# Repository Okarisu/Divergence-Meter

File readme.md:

# Divergence meter

## from Steins;Gate series and visual novels

## Note - this `readme` is in process of writing, the same as the code

## Basic synopsis

In this project I am trying to build working prototype of Divergence meter that appeared in Steins;Gate anime series and Visual novels.

I use arduino board in combination with shift registers SN74HC595N to drive itrons IV-6.

## byte values for shift registers

### Grids

| Itron No. | byte value |
| --------- | ---------- |
| first |  B01111111 |
| second | B10111111 |
| third | B11011111 |
| fourth | B11101111 |
| fifth | B11110111 |
| sixth | B11111011 |
| seventh | B11111101 |
| eighth | B11111110 |

### Numbers & symbols

| Number | byte value |
| ------ | ---------- |
| zero | B00000011 |
| one | B10011111 |
| two | B00100101 |
| three | B00001101 |
| four | B10110001 |
| five | B01001001 |
| six | B01000001 |
| seven | B00011111 |
| eight | B00000001 |
| nine | B00001001 |

| symbol | byte value |
| ------ | ---------- |
| dot | B11111110 |
| stroke | B11111101 |

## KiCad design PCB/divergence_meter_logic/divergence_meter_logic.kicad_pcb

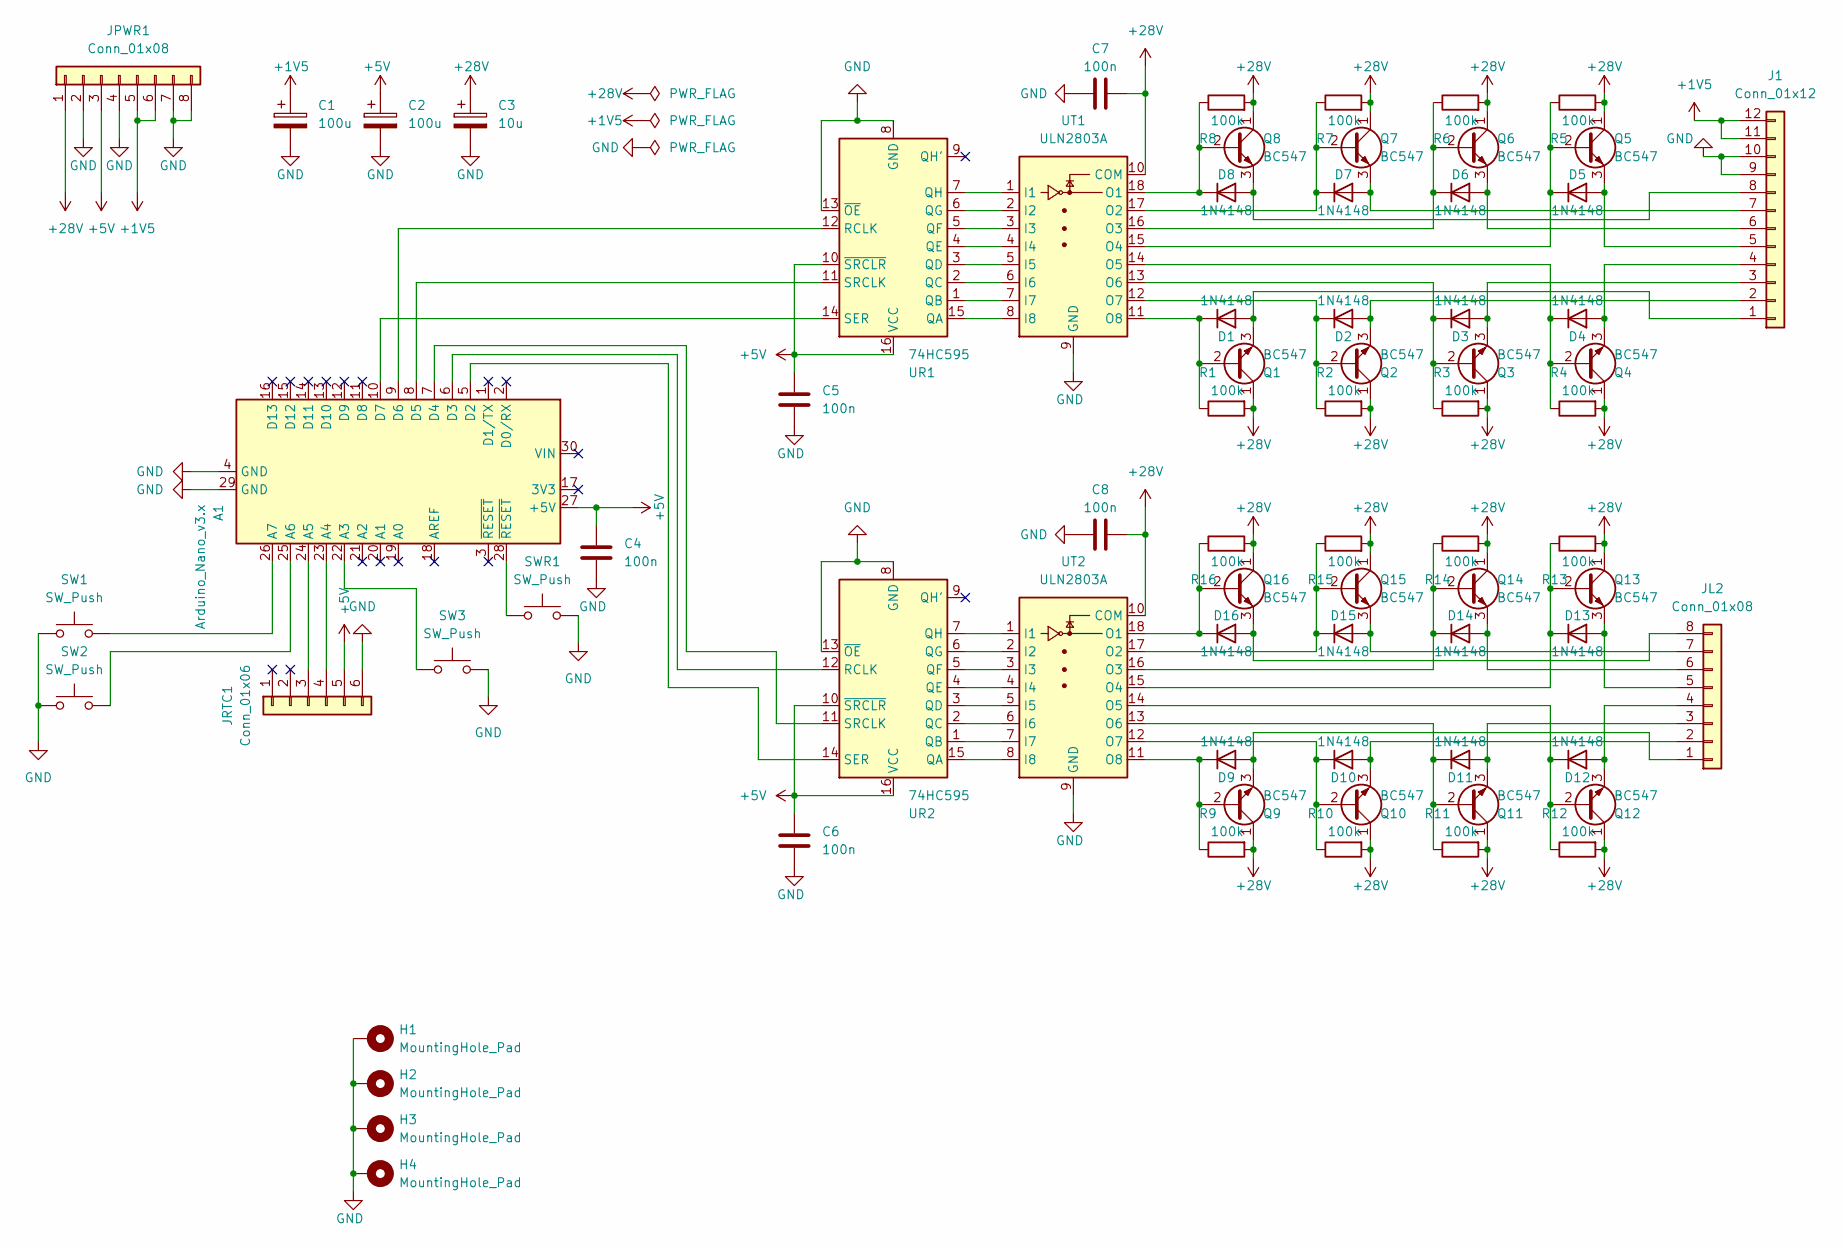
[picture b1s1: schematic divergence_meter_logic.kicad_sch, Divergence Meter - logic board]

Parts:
A1: Arduino_Nano_v3.x; Arduino_Nano
C1, C2: 100u; CP_Radial_D5.0mm_P2.00mm
C3: 10u; CP_Radial_D5.0mm_P2.00mm
C4, C5, C6, C7, C8: 100n; C_Disc_D5.0mm_W2.5mm_P5.00mm
D1, D2, D3, D4, D5, D6, D7, D8, D9, D10, D11, D12, D13, D14, D15, D16: 1N4148; D_DO-35_SOD27_P2.54mm_Vertical_KathodeUp
H1, H2, H3, H4: MountingHole_Pad; MountingHole_3.5mm_Pad_Via
J1: Conn_01x12; PinSocket_1x12_P2.54mm_Vertical
JL2: Conn_01x08; PinSocket_1x08_P2.54mm_Vertical
JPWR1: Conn_01x08; PinHeader_1x08_P2.54mm_Horizontal
JRTC1: Conn_01x06; PinSocket_1x06_P2.54mm_Horizontal
Q1, Q2, Q3, Q4, Q5, Q6, Q7, Q8, Q9, Q10, Q11, Q12, Q13, Q14, Q15, Q16: BC547; TO-92_Inline
R1, R2, R3, R4, R5, R6, R7, R8, R9, R10, R11, R12, R13, R14, R15, R16: 100k; R_Axial_DIN0204_L3.6mm_D1.6mm_P2.54mm_Vertical
SW1, SW2, SW3: SW_Push; SW_PUSH_6mm_H4.3mm
SWR1: SW_Push; SW_PUSH_6mm_H4.3mm
UR1, UR2: 74HC595; DIP-16_W7.62mm_Socket
UT1, UT2: ULN2803A; DIP-18_W7.62mm_Socket

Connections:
+1V5: C1.1, J1.11, J1.12, JPWR1.5, JPWR1.6
+5V: A1.27 (+5V), C2.1, C4.1, C5.1, C6.1, JPWR1.3, JRTC1.5, UR1.10 (~SRCLR), UR1.16 (VCC), UR2.10 (~SRCLR), UR2.16 (VCC)
+28V: C3.1, C7.2, C8.2, JPWR1.1, Q1.1 (C), Q2.1 (C), Q3.1 (C), Q4.1 (C), Q5.1 (C), Q6.1 (C), Q7.1 (C), Q8.1 (C), Q9.1 (C), Q10.1 (C), Q11.1 (C), Q12.1 (C), Q13.1 (C), Q14.1 (C), Q15.1 (C), Q16.1 (C), R1.2, R2.2, R3.2, R4.2, R5.2, R6.2, R7.2, R8.2, R9.2, R10.2, R11.2, R12.2, R13.2, R14.2, R15.2, R16.2, UT1.10 (COM), UT2.10 (COM)
GND: A1.4 (GND), A1.29 (GND), C1.2, C2.2, C3.2, C4.2, C5.2, C6.2, C7.1, C8.1, H1.1, H2.1, H3.1, H4.1, J1.9, J1.10, JPWR1.2, JPWR1.4, JPWR1.7, JPWR1.8, JRTC1.6, SW1.1, SW2.1, SW3.2, SWR1.2, UR1.8 (GND), UR1.13 (~OE), UR2.8 (GND), UR2.13 (~OE), UT1.9 (GND), UT2.9 (GND)
unnamed: A1.5 (D2), UR2.14 (SER)
unnamed: A1.6 (D3), UR2.12 (RCLK)
unnamed: A1.7 (D4), UR2.11 (SRCLK)
unnamed: A1.22 (A3), SW3.1
unnamed: A1.23 (A4), JRTC1.4
unnamed: A1.24 (A5), JRTC1.3
unnamed: A1.25 (A6), SW2.2
unnamed: A1.26 (A7), SW1.2
unnamed: A1.28 (~RESET), SWR1.1
unnamed: D1.1 (K), Q1.2 (B), R1.1, UT1.11 (O8)
unnamed: D1.2 (A), J1.1, Q1.3 (E)
unnamed: D2.1 (K), Q2.2 (B), R2.1, UT1.12 (O7)
unnamed: D2.2 (A), J1.2, Q2.3 (E)
unnamed: D3.1 (K), Q3.2 (B), R3.1, UT1.13 (O6)
unnamed: D3.2 (A), J1.3, Q3.3 (E)
unnamed: D4.1 (K), Q4.2 (B), R4.1, UT1.14 (O5)
unnamed: D4.2 (A), J1.4, Q4.3 (E)
unnamed: D5.1 (K), Q5.2 (B), R5.1, UT1.15 (O4)
unnamed: D5.2 (A), J1.5, Q5.3 (E)
unnamed: D6.1 (K), Q6.2 (B), R6.1, UT1.16 (O3)
unnamed: D6.2 (A), J1.6, Q6.3 (E)
unnamed: D7.1 (K), Q7.2 (B), R7.1, UT1.17 (O2)
unnamed: D7.2 (A), J1.7, Q7.3 (E)
unnamed: D8.1 (K), Q8.2 (B), R8.1, UT1.18 (O1)
unnamed: D8.2 (A), J1.8, Q8.3 (E)
unnamed: D9.1 (K), Q9.2 (B), R9.1, UT2.11 (O8)
unnamed: D9.2 (A), JL2.1, Q9.3 (E)
unnamed: D10.1 (K), Q10.2 (B), R10.1, UT2.12 (O7)
unnamed: D10.2 (A), JL2.2, Q10.3 (E)
unnamed: D11.1 (K), Q11.2 (B), R11.1, UT2.13 (O6)
unnamed: D11.2 (A), JL2.3, Q11.3 (E)
unnamed: D12.1 (K), Q12.2 (B), R12.1, UT2.14 (O5)
unnamed: D12.2 (A), JL2.4, Q12.3 (E)
unnamed: D13.1 (K), Q13.2 (B), R13.1, UT2.15 (O4)
unnamed: D13.2 (A), JL2.5, Q13.3 (E)
unnamed: D14.1 (K), Q14.2 (B), R14.1, UT2.16 (O3)
unnamed: D14.2 (A), JL2.6, Q14.3 (E)
unnamed: D15.1 (K), Q15.2 (B), R15.1, UT2.17 (O2)
unnamed: D15.2 (A), JL2.7, Q15.3 (E)
unnamed: D16.1 (K), Q16.2 (B), R16.1, UT2.18 (O1)
unnamed: D16.2 (A), JL2.8, Q16.3 (E)
unnamed: UR1.1 (QB), UT1.7 (I7)
unnamed: UR1.2 (QC), UT1.6 (I6)
unnamed: UR1.3 (QD), UT1.5 (I5)
unnamed: UR1.4 (QE), UT1.4 (I4)
unnamed: UR1.5 (QF), UT1.3 (I3)
unnamed: UR1.6 (QG), UT1.2 (I2)
unnamed: UR1.7 (QH), UT1.1 (I1)
unnamed: A1.8 (D5), UR1.11 (SRCLK)
unnamed: A1.9 (D6), UR1.12 (RCLK)
unnamed: A1.10 (D7), UR1.14 (SER)
unnamed: UR1.15 (QA), UT1.8 (I8)
unnamed: UR2.1 (QB), UT2.7 (I7)
unnamed: UR2.2 (QC), UT2.6 (I6)
unnamed: UR2.3 (QD), UT2.5 (I5)
unnamed: UR2.4 (QE), UT2.4 (I4)
unnamed: UR2.5 (QF), UT2.3 (I3)
unnamed: UR2.6 (QG), UT2.2 (I2)
unnamed: UR2.7 (QH), UT2.1 (I1)
unnamed: UR2.15 (QA), UT2.8 (I8)

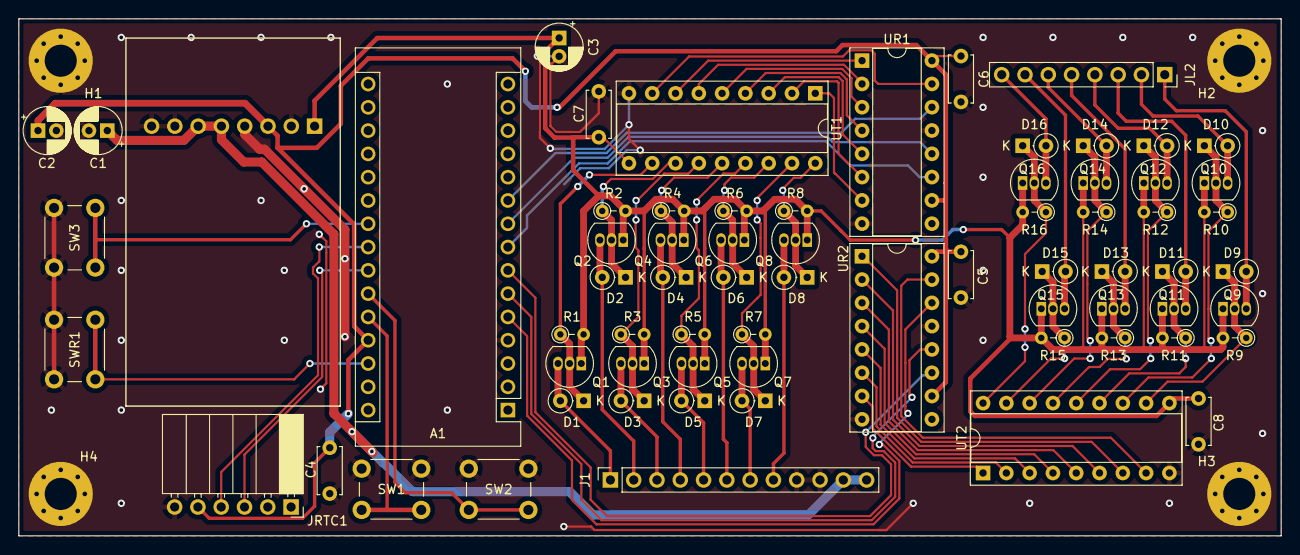
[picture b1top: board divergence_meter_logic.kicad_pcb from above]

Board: 2 copper layers, 137.7 x 56.4 mm, 73 parts (1 on the bottom side), 64 nets.

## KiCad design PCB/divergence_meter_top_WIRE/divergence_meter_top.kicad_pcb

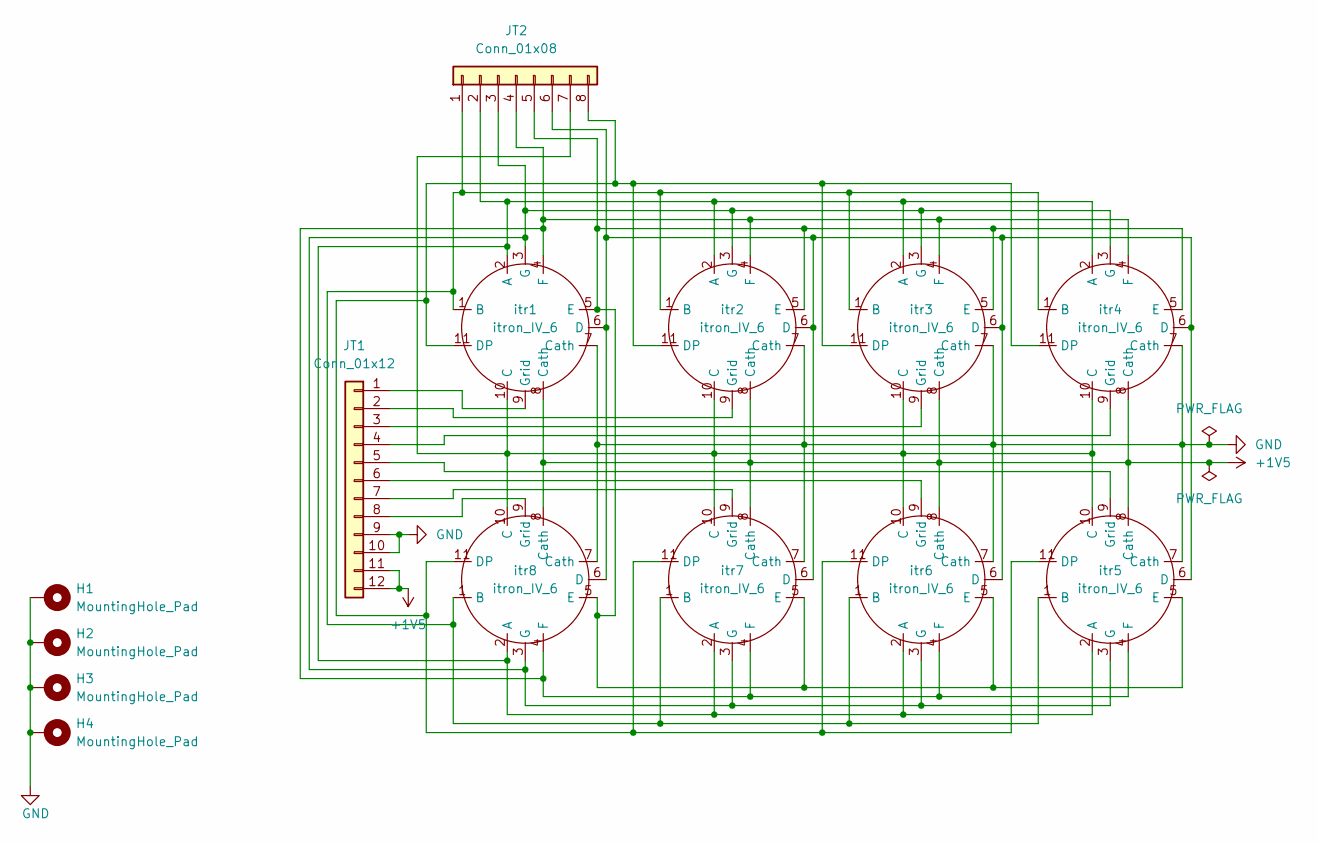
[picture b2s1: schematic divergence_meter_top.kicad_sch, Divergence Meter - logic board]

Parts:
H1, H2, H3, H4: MountingHole_Pad; MountingHole_3.5mm_Pad_Via
JT1: Conn_01x12; PinHeader_1x12_P2.54mm_Vertical
JT2: Conn_01x08; PinHeader_1x08_P2.54mm_Vertical
itr1, itr2, itr3, itr4, itr5, itr6, itr7, itr8: itron_IV_6

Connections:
+1V5: JT1.11, JT1.12, itr1.8 (Cath), itr2.8 (Cath), itr3.8 (Cath), itr4.8 (Cath), itr5.8 (Cath), itr6.8 (Cath), itr7.8 (Cath), itr8.8 (Cath)
GND: H1.1, H2.1, H3.1, H4.1, JT1.9, JT1.10, itr1.7 (Cath), itr2.7 (Cath), itr3.7 (Cath), itr4.7 (Cath), itr5.7 (Cath), itr6.7 (Cath), itr7.7 (Cath), itr8.7 (Cath)
unnamed: JT1.1, itr1.9 (Grid)
unnamed: JT1.2, itr2.9 (Grid)
unnamed: JT1.3, itr3.9 (Grid)
unnamed: JT1.4, itr4.9 (Grid)
unnamed: JT1.5, itr5.9 (Grid)
unnamed: JT1.6, itr6.9 (Grid)
unnamed: JT1.7, itr7.9 (Grid)
unnamed: JT1.8, itr8.9 (Grid)
unnamed: JT2.1, itr1.1 (B), itr2.1 (B), itr3.1 (B), itr4.1 (B), itr5.1 (B), itr6.1 (B), itr7.1 (B), itr8.1 (B)
unnamed: JT2.2, itr1.2 (A), itr2.2 (A), itr3.2 (A), itr4.2 (A), itr5.2 (A), itr6.2 (A), itr7.2 (A), itr8.2 (A)
unnamed: JT2.3, itr1.3 (G), itr2.3 (G), itr3.3 (G), itr4.3 (G), itr5.3 (G), itr6.3 (G), itr7.3 (G), itr8.3 (G)
unnamed: JT2.4, itr1.4 (F), itr2.4 (F), itr3.4 (F), itr4.4 (F), itr5.4 (F), itr6.4 (F), itr7.4 (F), itr8.4 (F)
unnamed: JT2.5, itr1.5 (E), itr2.5 (E), itr3.5 (E), itr4.5 (E), itr5.5 (E), itr6.5 (E), itr7.5 (E), itr8.5 (E)
unnamed: JT2.6, itr1.6 (D), itr2.6 (D), itr3.6 (D), itr4.6 (D), itr5.6 (D), itr6.6 (D), itr7.6 (D), itr8.6 (D)
unnamed: JT2.7, itr1.10 (C), itr2.10 (C), itr3.10 (C), itr4.10 (C), itr5.10 (C), itr6.10 (C), itr7.10 (C), itr8.10 (C)
unnamed: JT2.8, itr1.11 (DP), itr2.11 (DP), itr3.11 (DP), itr4.11 (DP), itr5.11 (DP), itr6.11 (DP), itr7.11 (DP), itr8.11 (DP)

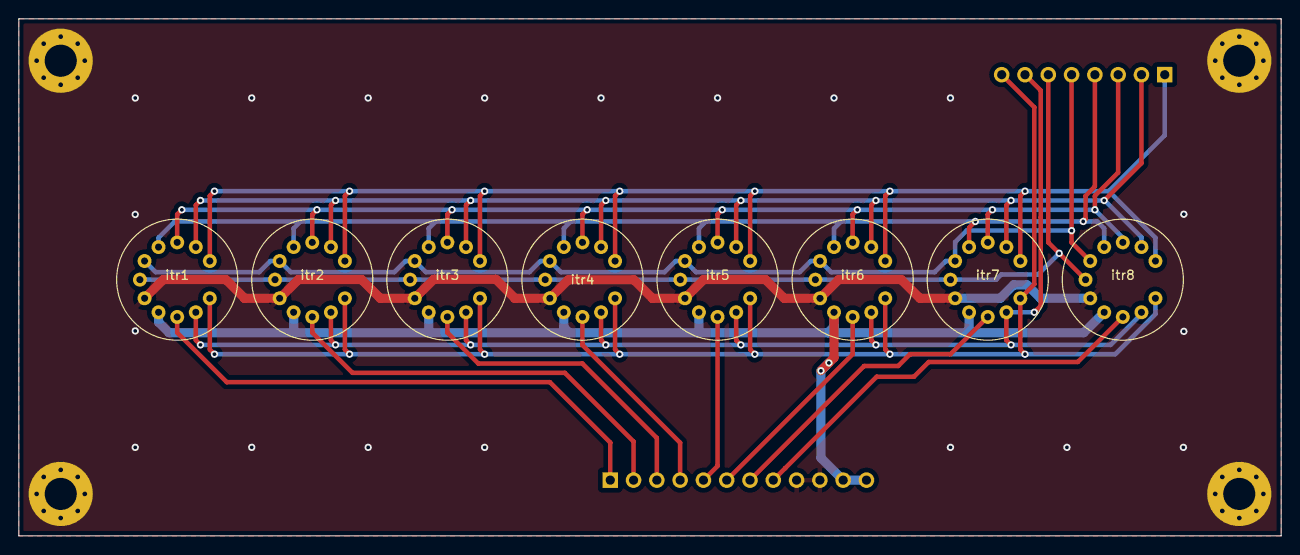
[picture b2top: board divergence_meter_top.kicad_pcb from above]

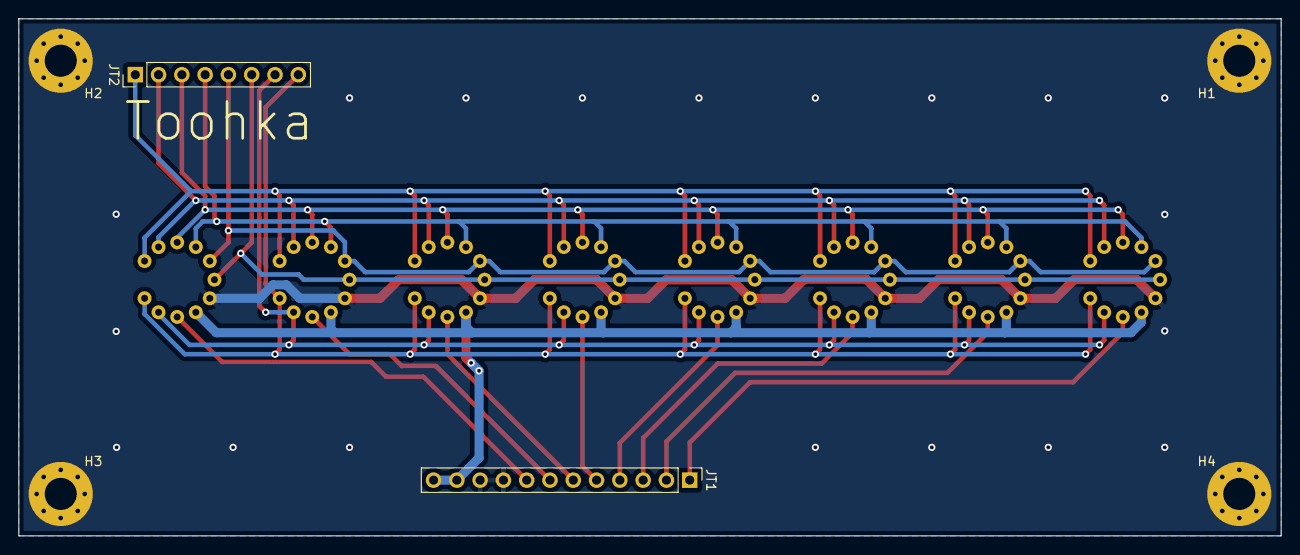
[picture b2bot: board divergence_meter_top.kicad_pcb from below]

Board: 2 copper layers, 137.7 x 56.4 mm, 14 parts (2 on the bottom side), 18 nets.

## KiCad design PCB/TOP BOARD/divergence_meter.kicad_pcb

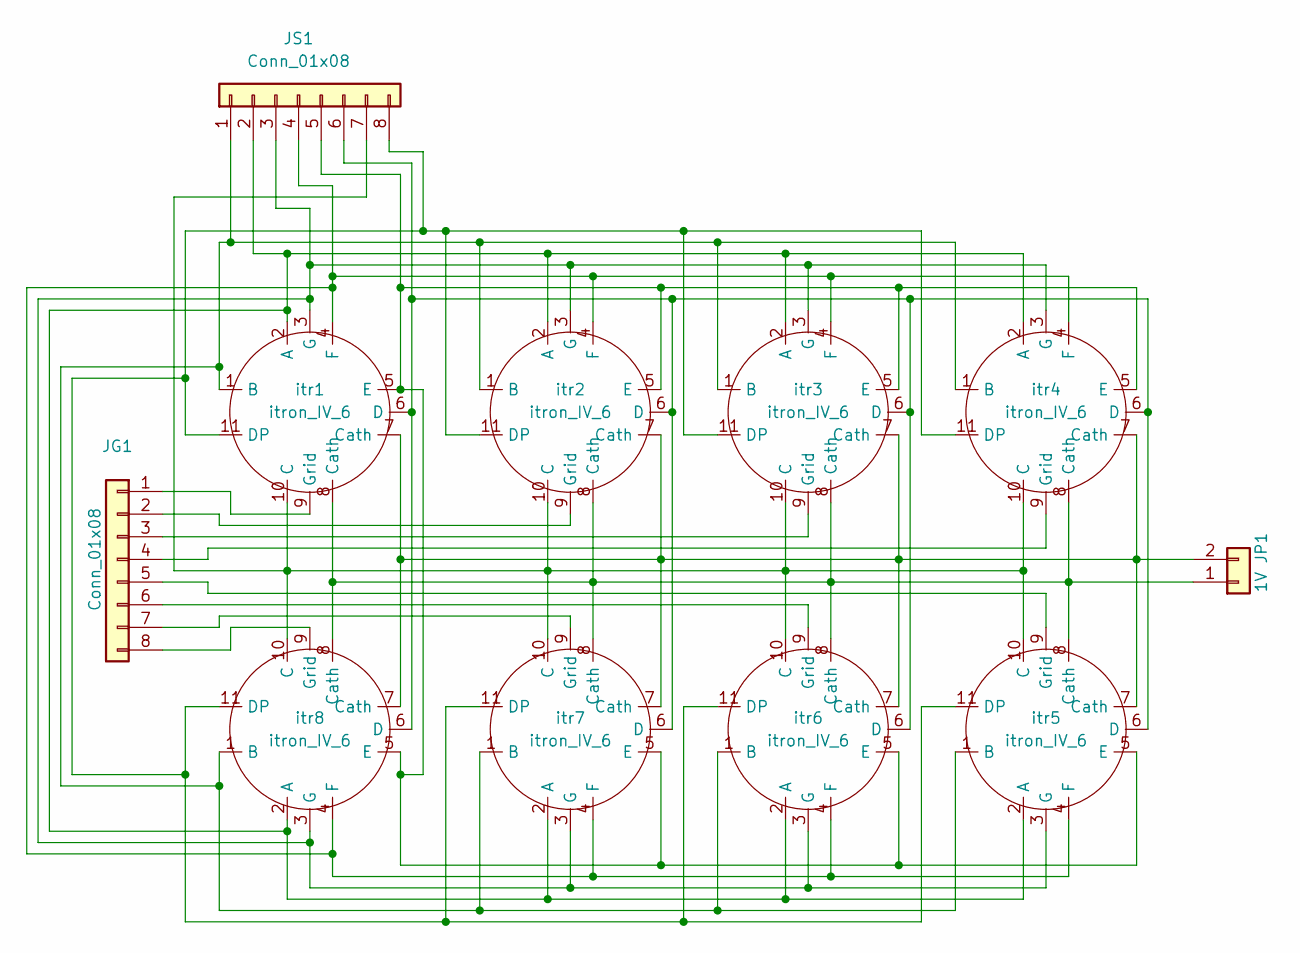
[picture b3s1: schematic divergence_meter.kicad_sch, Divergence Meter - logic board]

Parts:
JG1: Conn_01x08; PinHeader_1x08_P2.54mm_Vertical
JP1: 1V; PinHeader_1x02_P2.54mm_Vertical
JS1: Conn_01x08; PinHeader_1x08_P2.54mm_Vertical
itr1, itr2, itr3, itr4, itr5, itr6, itr7, itr8: itron_IV_6

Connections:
unnamed: JG1.1, itr1.9 (Grid)
unnamed: JG1.2, itr2.9 (Grid)
unnamed: JG1.3, itr3.9 (Grid)
unnamed: JG1.4, itr4.9 (Grid)
unnamed: JG1.5, itr5.9 (Grid)
unnamed: JG1.6, itr6.9 (Grid)
unnamed: JG1.7, itr7.9 (Grid)
unnamed: JG1.8, itr8.9 (Grid)
unnamed: JP1.1, itr1.8 (Cath), itr2.8 (Cath), itr3.8 (Cath), itr4.8 (Cath), itr5.8 (Cath), itr6.8 (Cath), itr7.8 (Cath), itr8.8 (Cath)
unnamed: JP1.2, itr1.7 (Cath), itr2.7 (Cath), itr3.7 (Cath), itr4.7 (Cath), itr5.7 (Cath), itr6.7 (Cath), itr7.7 (Cath), itr8.7 (Cath)
unnamed: JS1.1, itr1.1 (B), itr2.1 (B), itr3.1 (B), itr4.1 (B), itr5.1 (B), itr6.1 (B), itr7.1 (B), itr8.1 (B)
unnamed: JS1.2, itr1.2 (A), itr2.2 (A), itr3.2 (A), itr4.2 (A), itr5.2 (A), itr6.2 (A), itr7.2 (A), itr8.2 (A)
unnamed: JS1.3, itr1.3 (G), itr2.3 (G), itr3.3 (G), itr4.3 (G), itr5.3 (G), itr6.3 (G), itr7.3 (G), itr8.3 (G)
unnamed: JS1.4, itr1.4 (F), itr2.4 (F), itr3.4 (F), itr4.4 (F), itr5.4 (F), itr6.4 (F), itr7.4 (F), itr8.4 (F)
unnamed: JS1.5, itr1.5 (E), itr2.5 (E), itr3.5 (E), itr4.5 (E), itr5.5 (E), itr6.5 (E), itr7.5 (E), itr8.5 (E)
unnamed: JS1.6, itr1.6 (D), itr2.6 (D), itr3.6 (D), itr4.6 (D), itr5.6 (D), itr6.6 (D), itr7.6 (D), itr8.6 (D)
unnamed: JS1.7, itr1.10 (C), itr2.10 (C), itr3.10 (C), itr4.10 (C), itr5.10 (C), itr6.10 (C), itr7.10 (C), itr8.10 (C)
unnamed: JS1.8, itr1.11 (DP), itr2.11 (DP), itr3.11 (DP), itr4.11 (DP), itr5.11 (DP), itr6.11 (DP), itr7.11 (DP), itr8.11 (DP)

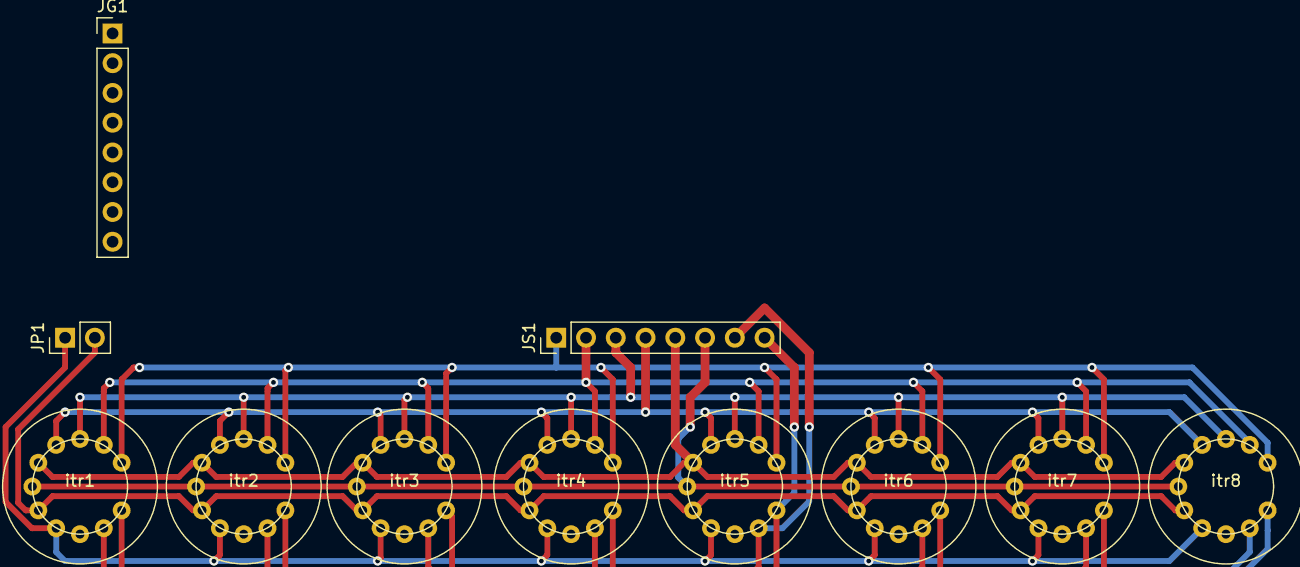
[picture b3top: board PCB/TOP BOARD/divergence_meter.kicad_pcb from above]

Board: 2 copper layers, 11 parts (0 on the bottom side), 18 nets.

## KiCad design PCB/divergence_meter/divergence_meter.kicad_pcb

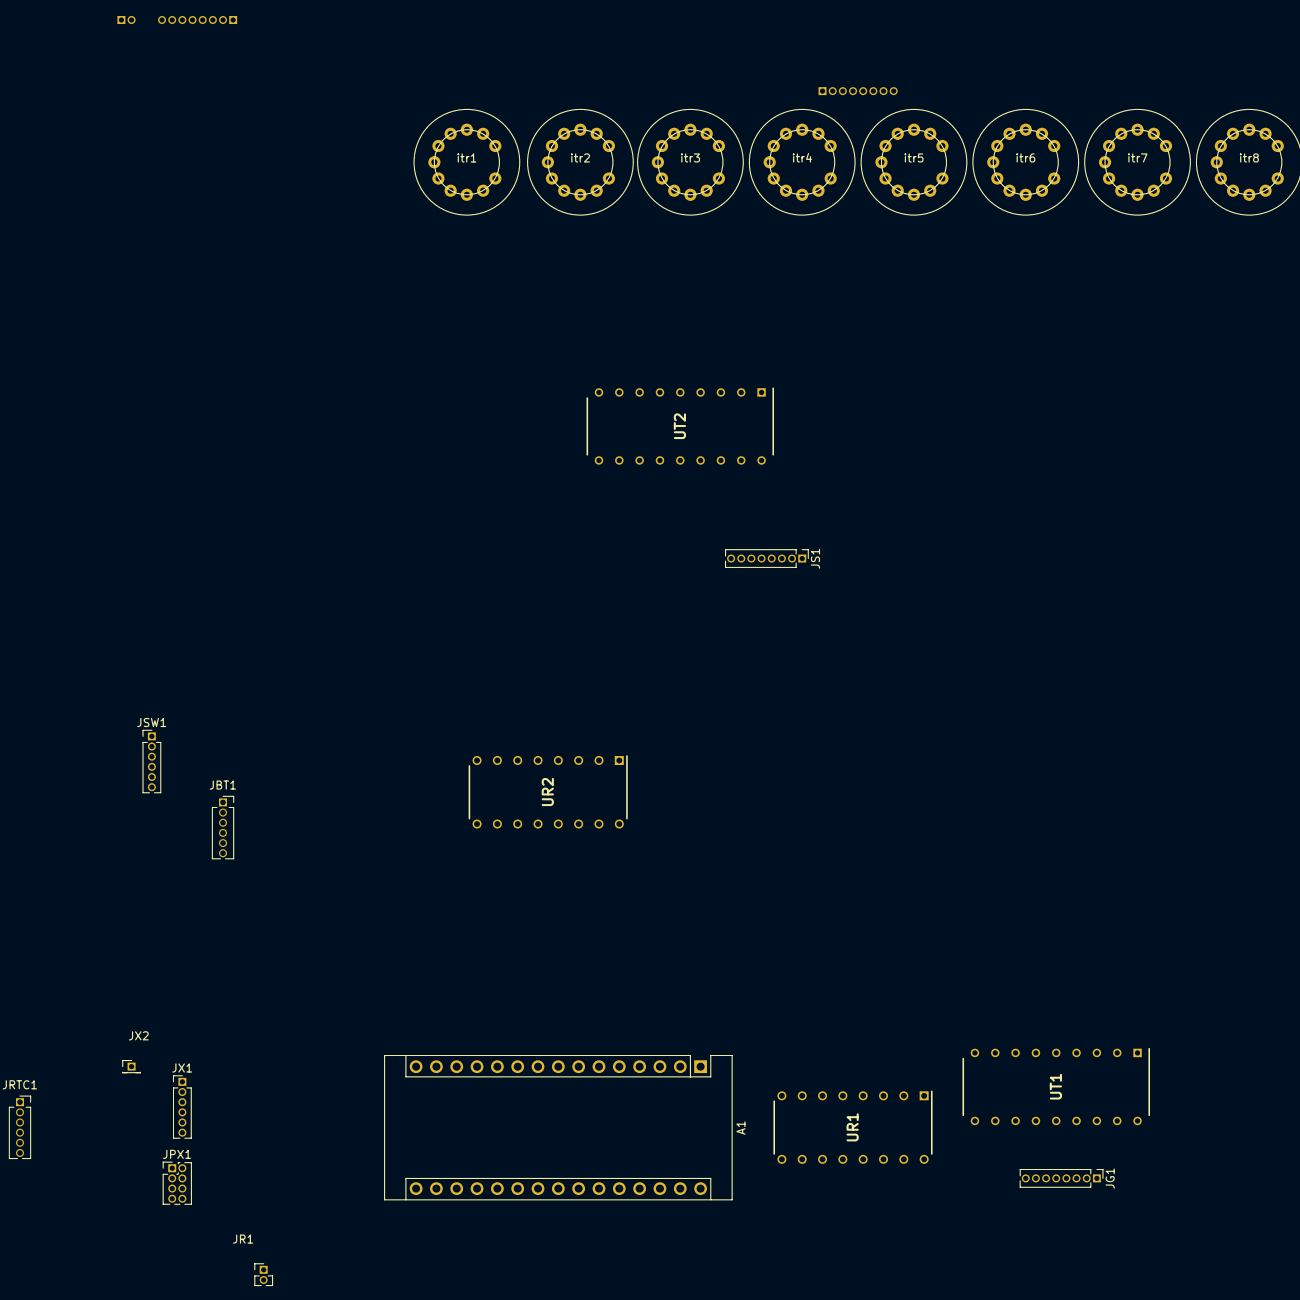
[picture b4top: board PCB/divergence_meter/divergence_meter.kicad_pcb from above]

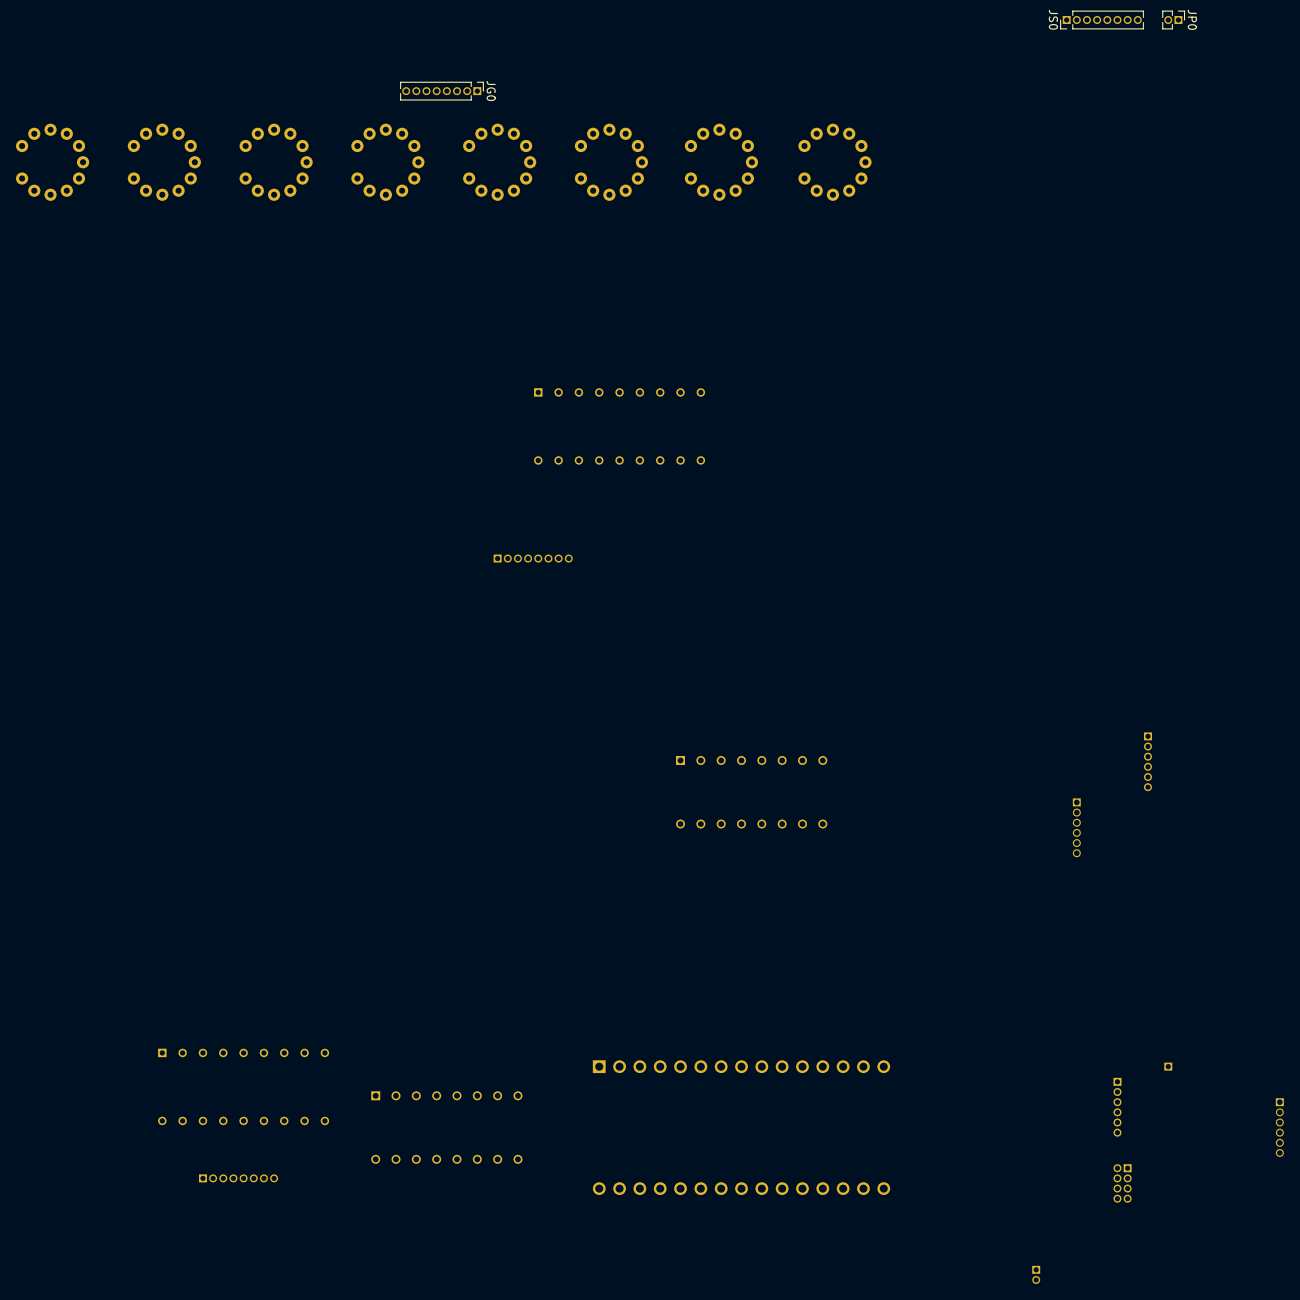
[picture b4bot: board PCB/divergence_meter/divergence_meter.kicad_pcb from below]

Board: 2 copper layers, 25 parts (3 on the bottom side), 74 nets, no tracks yet.

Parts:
A1: Arduino_Nano_v3.x; Arduino_Nano
JBT1: Conn_01x06; PinSocket_1x06_P1.27mm_Vertical
JG0, JG1: Conn_01x08; PinHeader_1x08_P1.27mm_Vertical
JP0: 1V; PinHeader_1x02_P1.27mm_Vertical
JPX1: Conn_02x04_Odd_Even; PinHeader_2x04_P1.27mm_Vertical
JR1: Conn_01x02; PinHeader_1x02_P1.27mm_Vertical
JRTC1: Conn_01x06; PinSocket_1x06_P1.27mm_Vertical
JS0, JS1: Conn_01x08; PinHeader_1x08_P1.27mm_Vertical
JSW1: Conn_01x06; PinHeader_1x06_P1.27mm_Vertical
JX1: Conn_01x06; PinHeader_1x06_P1.27mm_Vertical
JX2: Conn_01x01; PinHeader_1x01_P1.27mm_Vertical
UR1, UR2: 74HC595; DIP794W53P254L1930H508Q16N
UT1, UT2: ULN2803A; DIP850W46P254L2324H393Q18N
itr1, itr2, itr3, itr4, itr5, itr6, itr7, itr8: itron_IV_6

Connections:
+5V: A1.27 (+5V), JBT1.5, JPX1.1, JPX1.3, JPX1.5, JPX1.7, JRTC1.2, UR1.10 (~SRCLR), UR1.16 (VCC), UR2.10 (~SRCLR), UR2.16 (VCC)
GND: JP0.1, UT1.9 (GND), UT2.9 (GND), itr1.8 (Cath), itr2.8 (Cath), itr3.8 (Cath), itr4.8 (Cath), itr5.8 (Cath), itr6.8 (Cath), itr7.8 (Cath), itr8.8 (Cath)
GND1: A1.4 (GND), A1.29 (GND), JBT1.4, JPX1.2, JPX1.4, JPX1.6, JPX1.8, JR1.2, JRTC1.1, JSW1.2, JSW1.4, JSW1.6, UR1.8 (GND), UR1.13 (~OE), UR2.8 (GND), UR2.13 (~OE)
unnamed: A1.5 (D2), UR1.14 (SER)
unnamed: A1.6 (D3), UR1.12 (RCLK)
unnamed: A1.7 (D4), UR1.11 (SRCLK)
unnamed: A1.8 (D5), UR2.14 (SER)
unnamed: A1.9 (D6), UR2.12 (RCLK)
unnamed: A1.10 (D7), UR2.11 (SRCLK)
unnamed: A1.11 (D8), JBT1.2
unnamed: A1.12 (D9), JBT1.3
unnamed: A1.13 (D10), JSW1.1
unnamed: A1.14 (D11), JSW1.3
unnamed: A1.15 (D12), JSW1.5
unnamed: A1.16 (D13), JX2.1
unnamed: A1.19 (A0), JRTC1.3
unnamed: A1.20 (A1), JRTC1.4
unnamed: A1.21 (A2), JX1.1
unnamed: A1.22 (A3), JX1.2
unnamed: A1.23 (A4), JX1.3
unnamed: A1.24 (A5), JX1.4
unnamed: A1.25 (A6), JX1.5
unnamed: A1.26 (A7), JX1.6
unnamed: A1.28 (~RESET), JR1.1
unnamed: JG0.1, itr1.9 (Grid)
unnamed: JG0.2, itr2.9 (Grid)
unnamed: JG0.3, itr3.9 (Grid)
unnamed: JG0.4, itr4.9 (Grid)
unnamed: JG0.5, itr5.9 (Grid)
unnamed: JG0.6, itr6.9 (Grid)
unnamed: JG0.7, itr7.9 (Grid)
unnamed: JG0.8, itr8.9 (Grid)
unnamed: JG1.1, UT1.18 (O1)
unnamed: JG1.2, UT1.17 (O2)
unnamed: JG1.3, UT1.16 (O3)
unnamed: JG1.4, UT1.15 (O4)
unnamed: JG1.5, UT1.14 (O5)
unnamed: JG1.6, UT1.13 (O6)
unnamed: JG1.7, UT1.12 (O7)
unnamed: JG1.8, UT1.11 (O8)
unnamed: JP0.2, itr1.7 (Cath), itr2.7 (Cath), itr3.7 (Cath), itr4.7 (Cath), itr5.7 (Cath), itr6.7 (Cath), itr7.7 (Cath), itr8.7 (Cath)
unnamed: UT1.10 (COM), UT2.10 (COM)
unnamed: JS0.1, itr1.1 (B), itr2.1 (B), itr3.1 (B), itr4.1 (B), itr5.1 (B), itr6.1 (B), itr7.1 (B), itr8.1 (B)
unnamed: JS0.2, itr1.2 (A), itr2.2 (A), itr3.2 (A), itr4.2 (A), itr5.2 (A), itr6.2 (A), itr7.2 (A), itr8.2 (A)
unnamed: JS0.3, itr1.3 (G), itr2.3 (G), itr3.3 (G), itr4.3 (G), itr5.3 (G), itr6.3 (G), itr7.3 (G), itr8.3 (G)
unnamed: JS0.4, itr1.4 (F), itr2.4 (F), itr3.4 (F), itr4.4 (F), itr5.4 (F), itr6.4 (F), itr7.4 (F), itr8.4 (F)
unnamed: JS0.5, itr1.5 (E), itr2.5 (E), itr3.5 (E), itr4.5 (E), itr5.5 (E), itr6.5 (E), itr7.5 (E), itr8.5 (E)
unnamed: JS0.6, itr1.6 (D), itr2.6 (D), itr3.6 (D), itr4.6 (D), itr5.6 (D), itr6.6 (D), itr7.6 (D), itr8.6 (D)
unnamed: JS0.7, itr1.10 (C), itr2.10 (C), itr3.10 (C), itr4.10 (C), itr5.10 (C), itr6.10 (C), itr7.10 (C), itr8.10 (C)
unnamed: JS0.8, itr1.11 (DP), itr2.11 (DP), itr3.11 (DP), itr4.11 (DP), itr5.11 (DP), itr6.11 (DP), itr7.11 (DP), itr8.11 (DP)
unnamed: JS1.1, UT2.18 (O1)
unnamed: JS1.2, UT2.17 (O2)
unnamed: JS1.3, UT2.16 (O3)
unnamed: JS1.4, UT2.15 (O4)
unnamed: JS1.5, UT2.14 (O5)
unnamed: JS1.6, UT2.13 (O6)
unnamed: JS1.7, UT2.12 (O7)
unnamed: JS1.8, UT2.11 (O8)
unnamed: UR1.1 (QB), UT1.2 (I2)
unnamed: UR1.2 (QC), UT1.3 (I3)
unnamed: UR1.3 (QD), UT1.4 (I4)
unnamed: UR1.4 (QE), UT1.5 (I5)
unnamed: UR1.5 (QF), UT1.6 (I6)
unnamed: UR1.6 (QG), UT1.7 (I7)
unnamed: UR1.7 (QH), UT1.8 (I8)
unnamed: UR1.15 (QA), UT1.1 (I1)
unnamed: UR2.1 (QB), UT2.2 (I2)
unnamed: UR2.2 (QC), UT2.3 (I3)
unnamed: UR2.3 (QD), UT2.4 (I4)
unnamed: UR2.4 (QE), UT2.5 (I5)
unnamed: UR2.5 (QF), UT2.6 (I6)
unnamed: UR2.6 (QG), UT2.7 (I7)
unnamed: UR2.7 (QH), UT2.8 (I8)
unnamed: UR2.15 (QA), UT2.1 (I1)

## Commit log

2021-01-14 First push
2021-06-13 change deployment from LED to Itron version
2021-06-26 add conditions for time
2021-06-26 neco
2021-06-26 number change for
2021-06-27 just coding
2021-06-27 created time. and divergence. ino - separating functions
2021-06-27 corrected array positions
2021-07-01 rujn
2021-07-01 coding
2021-07-22 completed getTime fction, started divergence fction
2021-07-22 updated notes, work on divergence fction, updated variables positions (global -> local)
2021-07-30 split lang versions, corrected display position
2021-07-30 corrections
2021-08-16 finished divergence
2021-09-17 dokončen meter scratch soubor
2021-10-01 coding a už to funguje sakra
2021-10-02 controller
2021-10-08 finally compiled
2021-10-13 dunno
2021-10-15 renaming variables & functions #1
2022-01-07 všehocommit
2022-03-04 schematics
2022-03-05 Finished schematics, started PCB design
    Some schematics changes may be added
2022-03-06 working on PCB - itron board almost done
2022-03-09 itrons done, started logics
2022-05-11 skoro hotova horní deska
2022-05-27 fakt nevim
2022-05-27 Dokončena horní deska
2022-05-27 initial coding
2022-05-27 kicad refactor
2022-05-27 remake pcb
2022-06-01 code rework - display & time
2022-06-16 blah
2022-06-17 wuzah
2022-06-19 pcb rework
2022-06-19 pcb finishing
2022-06-23 logic pcb almost finished, remaking top
2022-06-23 top done, logic almost
2022-06-24 PCB done, exported gerber
2022-07-30 code
2023-02-17 reviewed logic board
2023-02-17 reviewing top board
2023-02-20 gitignore policies, kicad backups
2023-02-22 testing silkscreen images
2023-03-03 reviewed, schemes ok
2023-03-03 refactoring
2023-03-03 pinout
